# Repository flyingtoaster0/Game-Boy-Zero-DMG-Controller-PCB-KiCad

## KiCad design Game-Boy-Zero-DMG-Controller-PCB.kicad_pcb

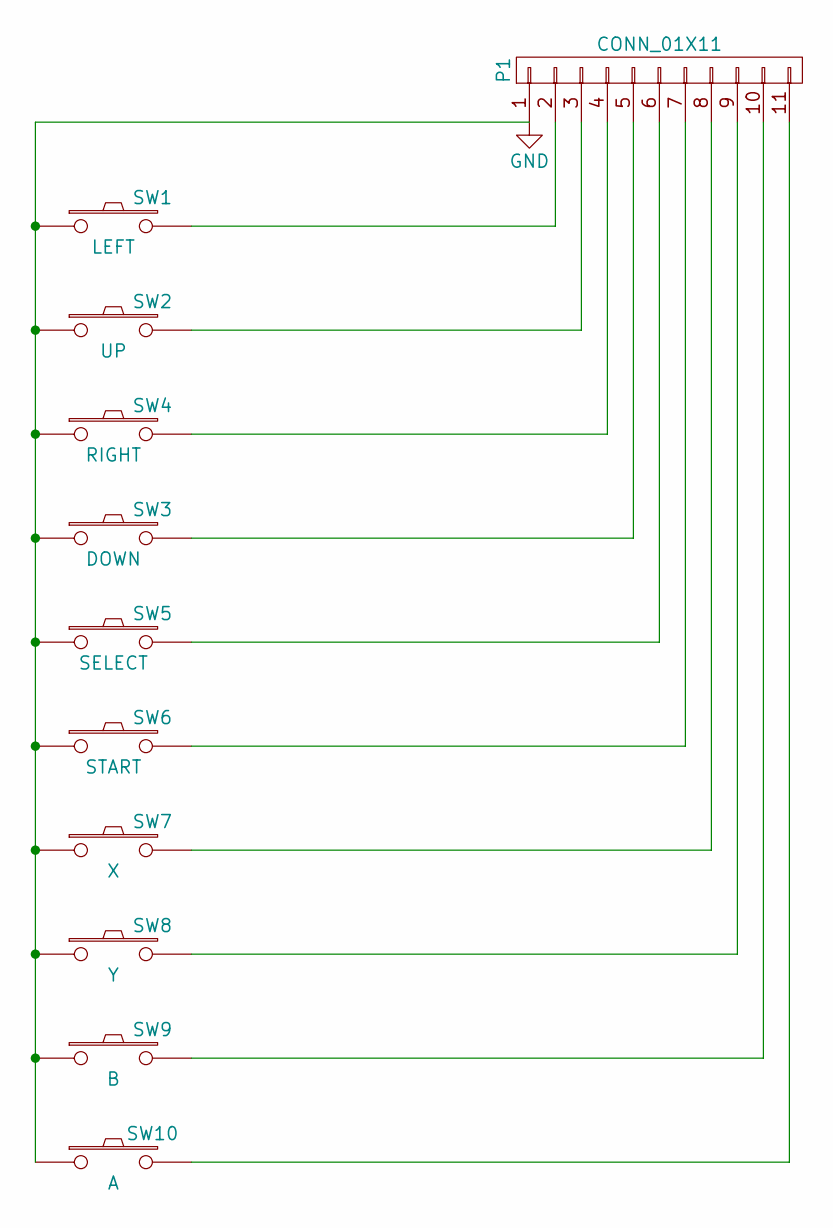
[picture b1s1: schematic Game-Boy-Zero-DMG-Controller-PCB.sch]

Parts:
P1: CONN_01X11; Socket_Strip_Straight_1x11
SW1: LEFT; GameBoy-DMG-BTN
SW2: UP; GameBoy-DMG-BTN
SW3: DOWN; GameBoy-DMG-BTN
SW4: RIGHT; GameBoy-DMG-BTN
SW5: SELECT; GameBoy-DMG-SEL
SW6: START; GameBoy-DMG-ST
SW7: X; GameBoy-DMG-BTN
SW8: Y; GameBoy-DMG-BTN
SW9: B; GameBoy-DMG-BTN
SW10: A; GameBoy-DMG-BTN

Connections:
GND: P1.1, SW1.1, SW2.1, SW3.1, SW4.1, SW5.1, SW6.1, SW7.1, SW8.1, SW9.1, SW10.1
unnamed: P1.2, SW1.2
unnamed: P1.3, SW2.2
unnamed: P1.4, SW4.2
unnamed: P1.5, SW3.2
unnamed: P1.6, SW5.2
unnamed: P1.7, SW6.2
unnamed: P1.8, SW7.2
unnamed: P1.9, SW8.2
unnamed: P1.10, SW9.2
unnamed: P1.11, SW10.2

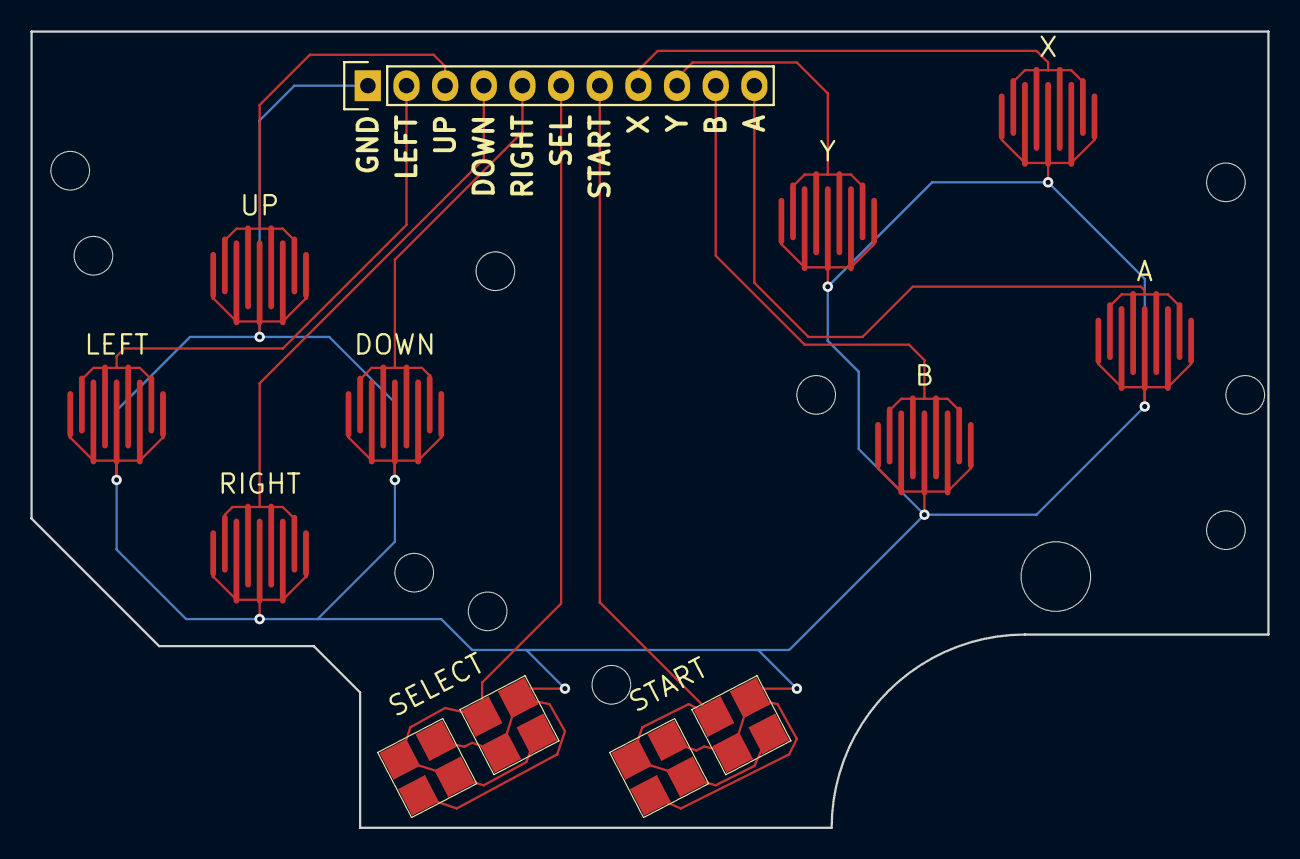
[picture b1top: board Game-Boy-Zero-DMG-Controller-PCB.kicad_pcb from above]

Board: 2 copper layers, 81.3 x 52.3 mm, 11 parts (0 on the bottom side), 11 nets.

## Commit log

2016-12-27 Add gitignore
2016-12-27 Add schematic and board
2016-12-27 All buttons wired. About to connect GND
2016-12-27 Route GND
2016-12-27 Sign my name so that everyone knows how legit I am
